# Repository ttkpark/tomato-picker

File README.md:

# tomato-picker

LG Physical AI 부스용 **토마토 따기 로봇** 데모 소프트웨어.
음성/텍스트 명령을 Claude가 받아 → 로봇이 색검출로 익은 토마토를 찾고 →
직접 따서 바구니에 담는다. (개념: *"언어 → 인식 → 행동"*)

> 설계 원칙: AI는 **두 층**(① 색 기반 열매 인식 ② Claude 함수콜 계획)에만.
> 이동·집기 등 저수준 동작은 **결정적 스킬 함수**로 처리한다.
> 자세한 배경은 [스마트로봇_명세서.md](스마트로봇_명세서.md), [PROJECT_토마토로봇.md](PROJECT_토마토로봇.md) 참고.

## 구조

```
main.py                         진입점 (demo / run)
src/tomato_picker/
├── config.py                   나무 위치·색 임계값·모델 ID
├── skills.py                   스킬 함수 5종 (핵심 API)
├── orchestrator.py             Claude tool-use 루프 (온라인)
├── demo_mode.py                오프라인 자동 시퀀스 (폴백, 필수)
├── hardware/                   하드웨어 추상화
│   ├── base.py                 인터페이스 (Base/Arm/Camera)
│   ├── mock.py                 PC용 Mock 구현
│   └── jetson.py               젯슨(실장비) 구현
└── vision/
    ├── color_detect.py         HSV 색검출 (빨강=익음/초록=미익음)
    └── claude_vision.py        Claude 비전 보조

firmware/mecanum_stable/        ✅ 현재 주행 펌웨어 (젯슨 시리얼 V/S 프로토콜, 데드맨+워치독) → firmware/README.md
tools/mirror_toggle.py          젯슨: SO-101 미러링 + 모션 프리셋 (PS2/키보드 연동, 리더 필요)
```

핵심: 스킬 함수 5종(`drive_to_tree` · `scan_tree` · `pick_fruit` ·
`place_in_basket` · `home`)을 온라인(Claude)과 오프라인(데모) 경로가
**공유**하므로 두 모드의 동작이 일관된다.

## 설치

```powershell
python -m venv .venv
.\.venv\Scripts\Activate.ps1
pip install -r requirements.txt
```

## 실행

```powershell
# 오프라인 데모 (망/API 키 불필요) — 지금 바로 실행 가능
python main.py demo

# Claude 오케스트레이션 (.env에 ANTHROPIC_API_KEY 필요)
copy .env.example .env   # 키 입력
python main.py run "익은 토마토 다 따줘"
```

현재는 **Mock 하드웨어**로 동작한다(합성 영상으로 색검출까지 전부 검증).
실제 장비가 오면 `main.py`의 `build_robot()`에서 하드웨어 구현만 교체한다.

## 하드웨어 제어 (실장비 — 메카넘 베이스 + SO-101 팔)

실장비는 **젯슨 Orin Nano**(JetPack)에서 구동한다. 두 갈래로 제어한다:

- **메카넘 베이스 + 팔 보조 입력** — Moebius Uno + PS2 패드. 펌웨어
  [firmware/PS2-MOTOR](firmware/PS2-MOTOR/) 가 PS2로 본체를 직접 굴리고, L1/R1 버튼은
  시리얼로 젯슨에 신호를 보낸다. 빌드·조작·핀맵은 [firmware/README.md](firmware/README.md).
- **SO-101 팔 (LeRobot)** — 리더→팔로워 텔레오프 미러링 + 모션 프리셋.
  젯슨에서 [tools/mirror_toggle.py](tools/mirror_toggle.py) 실행:

  | 조작 | 동작 |
  |---|---|
  | PS2 방향키 / □○ | 본체 주행 / 평행이동 |
  | **L1** | 팔 미러링 ON(리더 추종) ↔ OFF(limp) 토글 |
  | **R1 + △○✕□** | 미러링 ON: 현재 자세 **저장** / OFF: 저장 자세 **재생** (슬롯 1~4) |

  프리셋은 `~/arm_presets.json`에 영속. **토마토 따기 = 프리셋 1→2→3→4 순차 재생.**

> 셋업 메모(LeRobot 설치, 모터 ID·캘리브레이션, wrist_roll 엔코더 보정, CH340 드라이버
> 빌드 등)는 개발자 노트 참조. 실장비 구현은 `hardware/jetson.py`.

## 다음 단계

- [x] SO-101 팔 셋업(모터 ID·캘리브레이션) + 텔레오프 미러링 + 모션 프리셋
- [x] 메카넘 베이스 PS2 주행 펌웨어
- [ ] 모션 프리셋 시퀀스 **원버튼 자동 재생**(1→2→3→4) — 반복 수확
- [ ] 비전(토마토 검출) → 팔 동작 좌표 연동 / 시퀀스 자동 트리거
- [ ] `hardware/jetson.py`를 스킬 함수(`pick_fruit` 등)에 완전 연결
- [ ] 색 임계값을 실제 조명/열매로 튜닝 (`config.py`)
- [ ] (선택) 음성 입력(STT) → `run` 명령 연결

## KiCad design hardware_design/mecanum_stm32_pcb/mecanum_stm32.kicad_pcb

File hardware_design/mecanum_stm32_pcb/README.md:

# 메카넘 STM32 주행보드 (Uno + Moebius 쉴드 대체)

[docs/stm32-자세보드-목표.md](../../docs/stm32-자세보드-목표.md) 2단계(G2 엔코더 4채널 + G4 전원 도메인 분리)를 하는 보드.
펌웨어 = [firmware/mecanum_stm32/](../../firmware/mecanum_stm32/) (mecanum_stable v2.1 프로토콜 그대로 → 젯슨 코드 수정 없음).
요구사항 = [명세서 v0.2](../../docs/STM32_메카넘_베이스컨트롤러_명세서.md) (v0.1 항목별 반영 결과는 거기 §6).

- `gen_pcb.py` = **회로도 겸 배치**. 부품·넷·자리를 여기서 정하고 돌리면 `mecanum_stm32.kicad_pcb`가 다시 나온다.
  `"C:/Program Files/KiCad/9.0/bin/python.exe" gen_pcb.py` (겹침 0이어야 끝). `.kicad_sch`는 없다.
- 지금 상태(2026-11-09 **검토 반영 개정**): 148부품(고정구멍 포함), 선분 1,970 · 비아 160 — **kicad-cli DRC 오류 0 · 미연결 0**(`--severity-error`),
  `route.py check` 통과: 선 ≥0.127mm(최소 0.127) · 드릴 ≥0.3mm(최소 0.30) · USB 넷↔나머지 동박 ≥1.50mm · 디커플링 최악 2.85mm(≤3).
  전원 면 최소 폭(F.Cu, 1oz 기준 판단): VBAT_IN 2.6 · VBAT_R 2.4 · VBAT_P 2.4(K1 COM까지 3.2) · VM 릴레이→각 드라이버 탭 2.4 ·
  탭→핀 11 0.97(핀 끝에서 ≈1.65mm는 0.45mm 넥 — 핀 12·10 사이로 들어가는 입구) · 모터 출력 1.0mm(패드에서 0.76mm만 0.4mm 넥).
  거버 = [`gerber/`](gerber/)(2026-11-09 재생성, 같은 층·드릴 옵션). `placement.png` = 윗면 3D 렌더. 케이스 v2의 100×70 칸·Uno 구멍 그대로.
  **11/09에 바뀐 것과 이유**(검토 보고 → 결정):
  · 배치를 절대 mm로 다시 — 예전엔 Uno 비율로 늘린 좌표 + 30mm 나선 정착이라 U12 차지펌프 캡이 34mm, VCAP1 17mm, 크리스털 13mm 떨어져 있었다.
    IC마다 디커플링·타이밍 부품을 핀 기준 상대 좌표로 묶어 고정하고, 정착은 3mm 이내·고정 부품 불가, **배치 뒤 거리 검사(3mm)가 실패하면 종료코드 1**.
    예외: 드라이버 VM 벌크 C43/C47/C51/C55(10µF)는 핀 11에서 ≈4.1mm — 100nF(C42 등)가 1.9mm에 있고 차지펌프 캡 셋과 출력선이 3mm 안을 다 쓴다.
  · 전원: 예전 VM 0.19mm·VBAT_P 0.3mm 병목(정지 시 9.2A) → **F.Cu 동박 면**(VBAT_IN/VBAT_R/VBAT_P/VM: 위·아래 가장자리 띠 + 오른쪽 기둥 + 드라이버마다 탭).
    전원 넷은 Freerouting이 배선하지 않는다 — 그 넷 패드를 전부 면 안에 두었다(R9·R11·R66·D3·C15·D1·R1 자리 이동). 모터 출력은 gen_pcb가 1.0mm로 미리 깐다.
  · B.Cu는 GND 동박이지만 신호 2층 배선이라 **통짜는 아니다**(B.Cu 신호선 ≈1.9m, GND 채움 ≈3,950mm² ≈ GND 칸의 60%, 7조각 — 모두 비아로 이어짐).
  · DFM: DRV8874 방열 비아 0.2mm×48 → **0.3/0.6mm×12**(비아 없는 풋프린트 + 스크립트가 넣음). 설계규칙(.kicad_pro): 선 0.127·드릴 0.3·비아 0.6·간격 0.13.
  · 절연: U5를 회전 0으로(1~4번=USB 칸) — 예전엔 90°라 GNDU·GND 동박이 0.2mm까지 붙어 있었다. Freerouting에 1.5mm 해자(양면 금지)를 주고, `check`가 USB 넷↔나머지 동박 거리를 잰다.
  · 회로: 소프트 스타트·R1 22k·AMS1117 탄탈·E-stop PTC·코일 제너·ADC 100nF·VDDA 2.2µF·15pF·15µH·출력 22µF×3·Cin 100nF·USBLC6(부품 표는 아래).
- 다시 만들기 (순서 중요 — `gen_pcb.py`가 저장하며 `.kicad_pro` 넷클래스를 덮어쓰고, `route.py`가 다시 넣는다):
  ```
  K="C:/Program Files/KiCad/9.0/bin/python.exe"
  "$K" gen_pcb.py                 # 배치(빈 판)
  FR="java -jar freerouting-2.5.0.jar --router.autorouter.max_passes=60 --router.optimizer.enabled=false --gui.enabled=false"
  "$K" route.py prep              # 넷클래스·설계규칙 + mecanum_stm32.dsn (1단계: 전원 면 = 무른 plane)
  $FR -de mecanum_stm32.dsn -do stage1.ses
  "$K" route.py prep2 stage1.ses  # 2단계: 전원 면 = F.Cu 금지 구역, 면을 침범한 1단계 배선만 빼고 씨앗으로
  $FR -de mecanum_stm32.dsn -do mecanum_stm32.ses
  #   ⚠ optimizer를 켜 두면 최적화 단계에서 멈춰 .ses가 안 써진다(2026-11-02, 3회)
  #   ⚠ 1단계만 쓰면 Freerouting이 plane을 '나중에 다시 채울 동박'으로 보고 다른 넷을 그 위로 지나가게 해 전원 면이 끊긴다.
  #     처음부터 금지 구역으로 주면 배선이 발산한다(미배선 30~170을 오감) → 두 단계(11/09)
  "$K" route.py finish            # .ses 가져오기 → 가는 조각·곁가지 굵히기 → 전원 면(F.Cu) + GND 동박(양면) → 저장
  "$K" route.py check             # 선 ≥0.127 · 드릴 ≥0.3 · 절연 1.5mm · 디커플링 3mm · 전원 면 최소 폭
  kicad-cli pcb drc --severity-error --exit-code-violations mecanum_stm32.kicad_pcb
  ```
  `gen_pcb.py`는 겹침·절연 칸·**디커플링 거리(IC 핀 패드 ↔ 부품 패드 가장자리 ≤3mm)** 중 하나라도 어기면 종료코드 1로 멈춘다.
  배치를 안 바꿨으면 Freerouting 없이 저장소의 `mecanum_stm32.ses`(2단계 결과)로 `gen_pcb.py` → `route.py finish`만 하면 같은 판이 나온다.
  ⚠ KiCad 9.0.4의 `pcbnew.ExportSpecctraDSN`은 헤드리스에서 멈춰서 DSN/SES 변환을 `route.py`에 직접 짰다.

## 무엇을 왜 골랐나

| 자리 | 부품 | 왜 |
|---|---|---|
| MCU | **STM32F405RGT6** (LQFP64 0.5mm) | 엔코더 모드 타이머 4개(TIM2·3·4·5)를 다 쓰고도 PWM용 TIM8(4ch)·TIM9·TIM12가 남는다. F103은 TIM1~4뿐이라 엔코더 4개를 쓰면 PWM이 없고, F411은 TIM8이 없어 PWM이 TIM1(=USART1 PA9/PA10)과 겹친다. 엔코더 핀은 전부 5V 톨러런트(FT) |
| 모터 드라이버 ×4 | **DRV8874PWPR** (HTSSOP-16) | VM 37V(레일 12.6V의 ×2.9 — 목표 G4 "≥1.5배"), 6A 피크, **IPROPI 전류 감지 → ADC**, **nFAULT**, 내부 전류 제한(VREF). 지금 HR8833은 10.8V 정격에 12V를 물려 7/29에 탔다 |
| 젯슨 링크 | **CH340C + ADuM1201** | CH340C는 USB 전원(VBUS)으로, ADuM1201이 UART 두 가닥만 건넌다 → **젯슨 GND와 모터 GND가 끊긴다**(USB 끊김 `-71`의 원인 = 접지 루프). 칩이 CH340이라 젯슨에선 똑같이 `/dev/ttyUSB0`(1a86:7523). DTR을 안 물려서 **포트를 열어도 리셋되지 않는다**(Uno는 리셋됐다) |
| 전원 스위치 | **Q1·Q4 AO4407A 소스 맞댄 쌍** + **J8** 2핀 헤더(잠금형 스위치) + **소프트 스타트**(C15 1µF·D9·R71) | 스위치는 게이트만 GND로 당긴다(R1 22k/R68 10k → Vgs −0.69·Vbat: 7.4V→−5.1V, 12.6V→−8.7V, 24V는 D1 12V 클램프). C15가 **켤 때만**(D9) Q4 게이트-드레인 밀러 용량으로 걸려 VBAT_P를 ≈0.8V/ms로 올린다 → 2.5mF 돌입 ≈2A·≈15ms(예전엔 하드 스위칭 수십~100A대). 끌 때는 D9가 막아 밀러가 R71 100k로만 걸리므로 부하 중에 꺼도 FET가 선형 구간에 오래 머물지 않는다 → 배터리 전류가 스위치를 안 지나 작은 패널 스위치로 되고, 꺼지면 대기전류 0. FET 하나로는 몸체다이오드로 새서 못 끈다. 선이 빠지면 꺼진다. ⚠ 이 보드만 끈다 — 젯슨이 따로 배터리에서 받으면 같이 안 꺼진다 |
| 전압 감시 | 배터리 PC4 · 모터 VM PC5(100k/10k) · **5V PB0**(10k/10k) · **3V3 = VREFINT**(핀 없음), 분압점마다 100nF(C35~C37) | 100k/10k(9.1kΩ)는 ADC 샘플링 15사이클(21MHz)에서 겨우 들어간다 → 100nF가 전하를 대 준다.  하트비트 `vin= vm= v5= v33=`(mV) → 대시보드 비상정지 카드에 계통별 V. 상태 LED는 PB0→PB11로 옮겼다 |
| 전원 | AO4407A 역접속 보호(+스위치) → **VBAT_P**(1000µF 35V ×2, 배터리 감지 100k/10k) → **릴레이 K1** → VM(+SMBJ15A TVS) / VBAT_P → **SS34 + 470µF 홀드업** → **TPS542025**(5V 고정 벅, 4.5~30V) → AMS1117-3.3(출력 22µF 탄탈 C34 — AMS1117 안정 조건 ESR) | TPS542025: L1 **15µH**(TI 5V 표값) · 출력 22µF×3 · 입력 10µF+100nF를 VIN 핀 3mm 안에. 모터 기동으로 VM이 처져도 로직은 다이오드 뒤 홀드업으로 버틴다(지금 쉴드는 XL1509가 같이 무너져 BOD 리셋). 로직은 **릴레이 앞**에서 따서 비상정지 중에도 MCU·링크가 산다. 5V는 엔코더 전원(VCC50)도 겸한다 |
| 비상정지 | **K1 SRD-05VDC-SL-C**(10A/28VDC) + **F1 PTC 0.2A**(5V → E-stop 선, 선이 눌려 GND에 닿아도 5V 레일이 안 무너진다) + J6 단자(외부 NC 버튼, 없으면 단락) + 코일 역기전력 **D7 1N4148W + D8 12V 제너**(음극끼리 직렬 → 코일이 −12.5V까지 내려가 접점이 빨리 떨어진다. PB13엔 R60 10k 너머 ≈1.2mA 음주입 — F4 FT 핀 한계 5mA 안) + 코일 감지 → PB13 + **릴레이 뒤 VM 감지 → PC5**(100k/10k, 접점 용착 검출) + **VM 방전 2kΩ**(R66+R67 1k×2, E-stop 때 VM을 ≈80 ms에 비워 용착 오판 방지) | 명세서: 버튼이 릴레이 코일(5V)을 끊으면 접점이 **VM을 물리적으로 끊는다**(MCU 무관). 벌크는 릴레이 **앞**(뒤에 두면 접점이 닫힐 때 돌입 전류로 붙을 수 있다) |
| 엔코더 | 1k 직렬 + 10k 풀업(3V3) → 타이머 엔코더 모드 | 인터럽트로 세지 않는다(펄스 손실 0, G2). 오픈컬렉터/푸시풀 둘 다 받는다. **실측(11/04)**: 모터 엔코더 C1·C2 = 0↔5V, GND 단락 전류 ≈500µA(±5%) → **모터 안에 10k 풀업(5V)이 있는 오픈컬렉터**, C1−C2 = +5/0/−5V(0V 구간 있음) → **2상(90°) 확인**. 낮음일 때 VCC 단락 112·120mA = 출력 트랜지스터가 제한 없이 끌어내린다 → 보드 쪽 **1k 직렬이 핀 오설정(출력 HIGH) 때 3.3mA로 막아 준다 — 빼지 말 것**. 커넥터 1~6번 핀 중심 10mm = **2.0mm 피치 → PH 2.0 6핀 확인**(J10~J13 그대로). 보드의 3V3 10k 풀업과 겹쳐도 핀은 높음 ≈4.1V(FT 핀이라 됨)·낮음 ≈0.5V(VIL ≈1V 아래), 3V3로 역류는 채널당 ≈80µA |
| 커넥터 | JST PH 6핀 ×4, 쉴드와 같은 순서 `M− · GND · ENC_B · ENC_A · 5V · M+` | 모터 선을 그대로 옮겨 꽂게. **11/04 대조 완료**: 쉴드 회로도 [ARDUINO_HR8833.pdf](../../firmware/MecanumRobot-Arduino-Uno-master/ARDUINO_HR8833.pdf) JP1 `1 M1− · 2 GND · 3 ENCODER1_B · 4 ENCODER1_A · 5 VCC50 · 6 M1+` = J10~J13 1~6번과 같다, 실물 플러그 핀 중심 10mm·하우징 폭 13.5mm = PHR-6(PH 2.0), 장바구니 16721463 = JST 정품 B6B-PH-K-S. 쉴드는 JP3·JP4 엔코더가 NC였지만 이 보드는 4개 다 받는다 |
| USB | **Mini-B**(Würth 65100516121, 0.8mm 피치 5핀 + 큰 고정탭) + **USBLC6-2SC6**(D+/D−/VBUS ESD, GNDU 쪽) | USB-C는 0.5mm 피치라 손땜이 어려워 바꿨다(CC 저항도 필요 없다). 완전 스루홀이 필요하면 Tensility 54-00023(세로형) |
| 젯슨 UART 직결(대안) | **J7** 1×4 헤더(GNDU · TX→ · ←RX · 3.3V) + R62~R64 0Ω | 명세서의 "젯슨 3.3V UART 직결"을 **절연기 앞**에 붙였다(젯슨 GND는 GNDU 칸에만 닿는다). 기본은 USB(R62~R64 실장). J7로 쓸 땐 R62~R64를 빼고 젯슨 포트를 `/dev/ttyTHS*`로 |
| 기타 | SWD 헤더, RESET/BOOT0 버튼, I²C 헤더(MPU6050 이전용), SPI IMU 헤더(오른쪽 헤더 줄), LED 3개 | 첫 굽기는 SWD 또는 BOOT0. 이후엔 젯슨에서 `U` 명령 → `stm32flash` |

판 = **100×70mm, 2층**. 고정구멍 4개는 **Uno와 같은 자리**(왼쪽 아래 기준)라 지금 스탠드오프에 앉는다.
Uno 크기(68.6×53.3)로는 2층 배선이 안 나와 키웠고(부품면적 67%), 명세서 반영(릴레이·벌크)으로 90×64에서 한 번 더 키웠다(지금 46%).

## 부품 주문 — 엘레파츠 장바구니 (2026-11-02, 34종 74,011원·무료배송, 발송 예정 11/13)

예비 포함 수량. 상품번호 = `https://www.eleparts.co.kr/goods/view?no=<번호>`.
디바이스마트는 조회 중 접속이 막혀(연속 요청 차단으로 보임) 이번엔 안 썼다.
⚠ **비회원 장바구니는 세션 쿠키라 브라우저를 닫으면 사라진다**(실제로 한 번 날아가 다시 담았다) — 로그인해서 담을 것.

| 품목 | 상품번호 | 수량 | 기판 |
|---|---|---|---|
| STM32F405RGT6 | 12074516 | 2 | U1 |
| DRV8874PWPR | 12217360 | 5 | U10~U13 |
| TPS542025DDCR | 18672221 | 2 | U2 |
| AMS1117-3.3 (UMW) | 7595038 | 10 | U3 |
| CH340C | 6557221 | 2 | U4 |
| ADUM1201ARZ (ADI) | 18290182 | 1 | U5 |
| AO4407A | 12744910 | 5 | Q1·Q4 |
| SMBJ15A (Littelfuse) | 6978442 | 5 | D2 |
| SS34 | 17819449 | 20 | D3, D7 |
| BZT52C12 | 16812906 | 5 | D1 |
| 8MHz 3225 12pF | 12209546 | 5 | Y1 |
| SRP7028A-100M 10µH | 2840708 | 2 | L1 |
| 470µF 25V 10×12.5 | 3369549 | 5 | C2 |
| 1000µF 35V 12.5×20 (삼영 KMG) | 9159533 | 5 | C1, C14 |
| 릴레이 SRD-05VDC-SL-C | 8570092 | 2 | K1 |
| USB Mini-B Würth 65100516121 | 69486 | 2 | J2 |
| JST B6B-PH-K-S | 16721463 | 5 | J10~J13 |
| KF301-5.0-2P | 10367448 | 5 | J1, J6 |
| B3F-1000 | 18219995 | 2 | SW1, SW2 |
| 핀헤더 1×40 | 16069834 | 1 | J3·J4·J5·J7·J8 (잘라 씀) |
| 0603 저항 10k / 1k / 47k / 100k / 0Ω | 9845055 / 9471061 / 16762241 / 16790845 / 14720542 | 각 100 | |
| 0603 100nF 50V / 22nF 50V / 2.2µF / 4.7µF / 20pF | 8010073 / 8010651 / 8011085 / 8010241 / 8010017 | 100/50/50/10/100 | |
| 1206 10µF 25V / 22µF 10V | 8010168 / 8010994 | 10 / 5 | |
| 0603 LED 초록 / 빨강 | 4996 / 4997 | 각 5 | D4·D5 / D6 |

### 2026-11-09 검토 반영으로 늘거나 바뀐 부품 — 11/09 비서가 로그인 계정 장바구니에 담음(9종 ≈12,612원, VAT 별도)

상품번호: SRP7028A-150M 12432675 · USBLC6-2SC6 18086957 · 탄탈 22µF 3528 6533815 · PTC 0.2A 0ZCJ0020FF2E 18218454 · 0603 15pF 2638972 · 0603 22k 18136622 · 0805 1µF 50V 18068538 · 1N4148W 16865523 · BZT52C12 17312667(3개).
⚠ 비서는 담을 때 **장바구니에 SRP7028A-100M·BZT52C12가 없었다**고 했다 — 11/02의 34종이 비회원 세션째 날아갔을 수 있다. 결제 전에 위 표와 대조할 것.

| 품목 | 수량(예비 포함) | 기판 | 비고 |
|---|---|---|---|
| SRP7028A-**150M** 15µH | 2 | L1 | 100M(10µH) 대신, 같은 풋프린트. 장바구니의 100M은 빼도 된다 |
| USBLC6-2SC6 | 3 | U6 | USB ESD |
| 22µF 10V 탄탈 EIA-3528(B) | 3 | C34 | AMS1117 출력 ESR |
| PTC 0.2A hold 1206 (예: Bel 0ZCJ0020FF2E) | 3 | F1 | 5V → E-stop 선. 코일 71mA에 R≤4Ω → 코일 4.7V 이상 |
| 0603 15pF | 10 | C28, C29 | 20pF 대신(CL 12pF 수정) |
| 0603 22k | 10 | R1 | 100k 대신 |
| **0805 1µF 50V X7R** | 5 | C15 | 소프트 스타트(지시의 47nF 대신 — 아래 이유) |
| 1N4148W (SOD-123) | 10 | D7, D9 | D7은 SS34(SMA) 대신 — 코일 71mA |
| BZT52C12 | +3 (총 8) | D8 | 장바구니 5개 → D1·D8 |
| 0603 100nF / 2.2µF / 22µF 1206 | 기존 수량 안 | C32·C35~C37 / C31 / C33 | 장바구니 수량으로 충분 |
| 0603 0Ω / 100k / 47k | 기존 수량 안 | R72~R74(칩마다 PMODE) / R75 / R76(아래 줄 VREF) | 장바구니 수량으로 충분 |

47nF가 아니라 1µF+다이오드인 이유: 게이트-드레인 47nF(R68 10k)면 VBAT_P가 ≈18V/ms로 올라 2.5mF 돌입이 ≈45A·0.7ms가 되고,
그동안 콘덴서 충전 에너지(½CV² ≈0.2J)를 **FET가 1ms 안에 다 먹는다**(SOIC-8 1ms SOA 밖일 공산이 크다, AO4407A SOA 그래프로 확인 요) —
하드 스위칭보다 나쁘다. 또 밀러 C가 끌 때도 걸려 22k로 끄면 부하 중 ≈4ms 선형 구간. 그래서 C15 1µF(≈15ms 램프, 돌입 ≈2A, FET 평균 ≈13W)를
D9로 **켤 때만** 걸고 R71 100k가 꺼진 뒤 원위치시킨다.

VREF·PMODE: 한 넷을 판 네 귀퉁이 드라이버로 끌면 MCU 둘레가 막혀 자동배선이 끝나지 않아(11/09) **VREF 분압을 위(A·B: R13/R14)·아래(C·D: R75/R76) 줄에 하나씩**, PMODE 0Ω을 칩마다(R16·R72~R74) 두었다(값·동작은 같다).
재고가 없어 바꾼 값: 20k→**100k/47k**(VREF 1.06V, 전류제한 ≈2.3A), 4.7k→**10k**(I²C 풀업 — MPU6050 모듈에도 있다),
배터리 분압은 명세서대로 **100k/10k**(÷11, 36V까지 — 펌웨어 `B`의 기본 비 11000).

## ⚠ 만들기 전에 확인할 것

1. **모터에 엔코더가 정말 있나, 커넥터가 PH 2.0mm인가** — 쉴드 회로도상 6핀이지만 실물 확인 전([목표 문서 §0.1](../../docs/stm32-자세보드-목표.md)).
   2.54mm(XH)면 J10~J13 풋프린트만 바꾸면 된다.
2. ~~DRV8874 PMODE·IMODE~~ → **데이터시트(SLVSF66A, 42쪽)로 확인함**: PMODE=High → PWM 모드(표 2, nSLEEP가 올라갈 때 래치 —
   nSLEEP 풀다운이라 순서 OK), IN1=PWM·IN2=0 → 정방향/코스트(표 4, Uno와 같은 동작), IMODE=GND → 고정 오프타임 초핑 +
   과전류 **자동 재시도**(표 6), A_IPROPI 450µA/A.
3. **케이스** — 옛 트레이에선 100×70이 배터리 턱을 15.6mm 넘었다(11/05 계산). [케이스 v2](../case/README.md)는 앞 가운데에 이 판 자리를 뒀다(같은 구멍, 간섭 검사 통과) → 판을 다시 배치하지 않는다.
   제조 한계(11/09 개정): 선 ≥0.127mm, 드릴 ≥0.3mm(DRV8874 방열 비아 0.3/0.6mm × 12개/칩) — 설계규칙(.kicad_pro)이 DRC로 강제한다.
   **주문 메모: 동박 2oz 권장**(전원 면·모터선 저항·온도 절반).
6. **배터리가 24V면**(6S 만충 25.2V) — 바꿀 것: TVS SMBJ15A→SMBJ24A, 470µF 25V→35V, 1206 10µF 25V→50V(C3·C43 등),
   **블리더 R66/R67 0603(100mW)→1206** 또는 2.2k×2(25.2V에서 0603 각 159mW로 정격 초과), **Q1/Q4 → −40V P-FET**(AO4407A −30V는 84% 사용),
   소프트 스타트 C15 1µF→2.2µF(돌입 에너지 0.72J — 램프를 늘려 FET 평균 전력을 맞춘다), R1 22k는 그대로(D1이 Vgs −12V로 묶음).
   ⚠ SMBJ24A는 정격 펄스에서 Vc 38.9V로 DRV8874 권장 37V(절대 40V)를 넘는다 — 6S면 SMBJ 계열로는 맞는 게 없으니 클램프를 다시 고를 것.
   TPS542025(30V)·벌크(35V)·릴레이(28VDC)·분압(36V까지)은 그대로.
7. **선택 사항(이번엔 안 넣음)**: IPROPI에 10nF(데이터시트 허용, 코스트 감쇠라 IPROPI가 PWM으로 끊긴다 — 펌웨어 슬로 감쇠나 동기 샘플링이 우선),
   엔코더 커넥터 5V(5번 핀, M+ 바로 옆)에 퓨즈/PTC.
4. **HTSSOP 방열 패드** — 인두로는 안 붙는다. 열풍기/리플로우, 또는 방열 비아로 뒤에서 땜.
5. **자동배선 결과를 사람 눈으로 한 번** — 크리스털 주변, 절연 경계(GNDU 동박은 USB 칸에만, GND와 1.5mm), 게이트·소프트 스타트 망(손으로 깐 선).
   고정구멍 둘레 Ø6.5mm는 동박 금지(나사머리·스탠드오프가 GNDU를 로봇 GND에 잇지 않게).
   신호 0.15mm(Freerouting 넥다운 조각은 finish가 0.127 이상으로 되돌림), 5V·3V3·GND 곁가지는 간격이 되는 곳만 0.5mm.

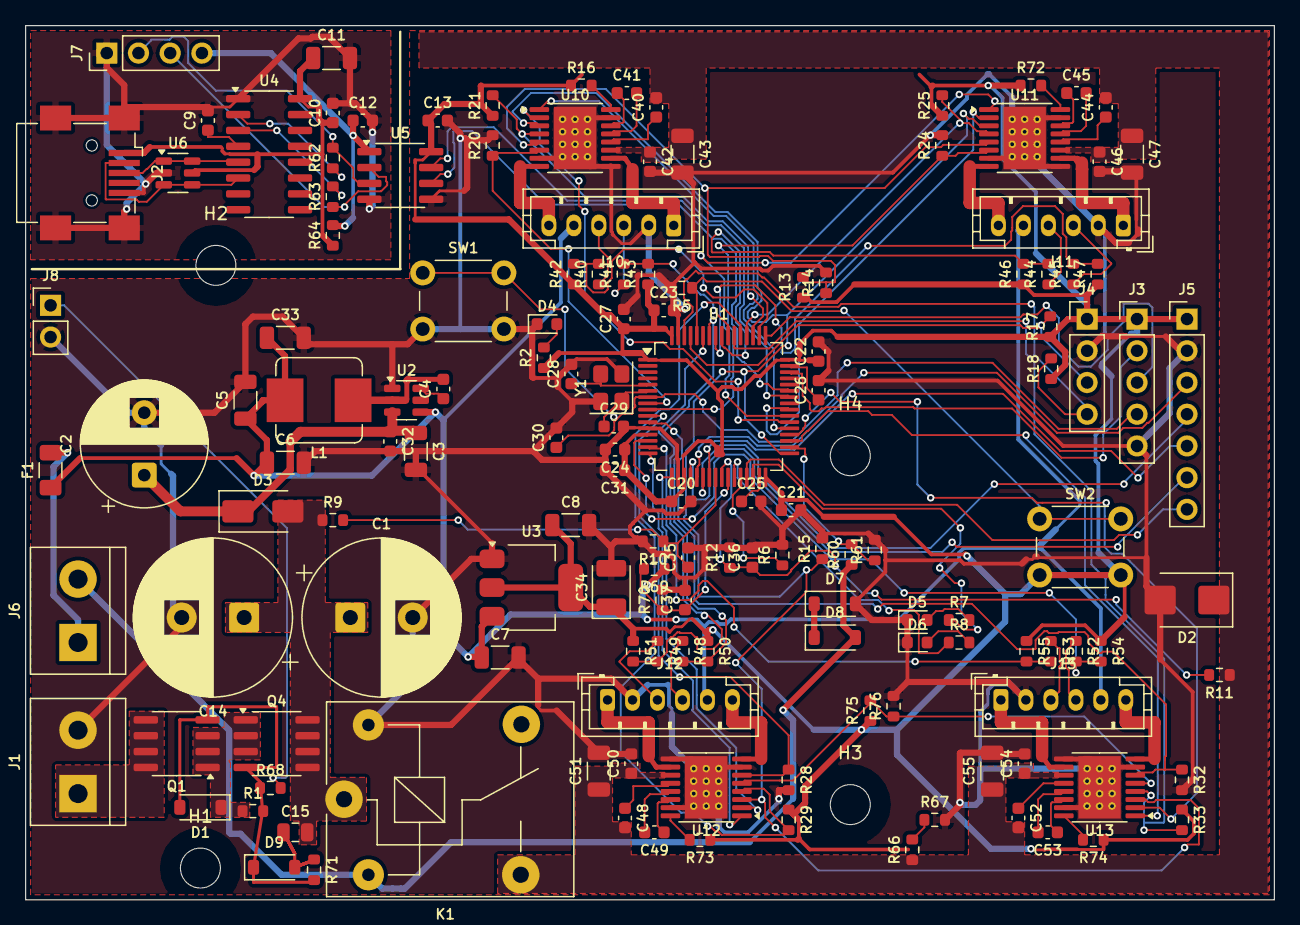
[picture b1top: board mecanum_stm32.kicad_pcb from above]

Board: 2 copper layers, 100.0 x 70.0 mm, 148 parts (0 on the bottom side), 113 nets.

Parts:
C1, C14: 1000u 35V; CP_Radial_D12.5mm_P5.00mm
C2: 470u 25V; CP_Radial_D10.0mm_P5.00mm
C3, C7, C8, C11, C43, C47, C51, C55: 10u 25V; C_1206_3216Metric
C4, C9, C10, C12, C13, C20, C21, C22, C23, C24, C30, C35, C36, C37: 100n; C_0603_1608Metric
C5, C6, C33: 22u 10V; C_1206_3216Metric
C15: 1u 50V X7R; C_0805_2012Metric
C25, C26, C31: 2.2u; C_0603_1608Metric
C27: 4.7u; C_0603_1608Metric
C28, C29: 15p; C_0603_1608Metric
C32, C40, C42, C44, C46, C48, C50, C52, C54: 100n 50V; C_0603_1608Metric
C34: 22u 10V tant; CP_EIA-3528-21_Kemet-B
C41, C45, C49, C53: 22n 50V; C_0603_1608Metric
D1, D8: BZT52C12; D_SOD-123
D2: SMBJ15A; D_SMB
D3: SS34; D_SMA
D4: PWR 초록; LED_0603_1608Metric
D5: 상태 초록; LED_0603_1608Metric
D6: 고장 빨강; LED_0603_1608Metric
D7, D9: 1N4148W; D_SOD-123
F1: PTC 0.2A hold; Fuse_1206_3216Metric
H1, H2, H3, H4: MountingHole_3.2mm_M3
J1: BAT 7.4~12.6V; TerminalBlock_bornier-2_P5.08mm
J2: USB Mini-B; USB_Mini-B_Wuerth_65100516121_Horizontal
J3: SWD; PinHeader_1x05_P2.54mm_Vertical
J4: I2C (MPU6050); PinHeader_1x04_P2.54mm_Vertical
J5: SPI IMU; PinHeader_1x07_P2.54mm_Vertical
J6: E-STOP (NC); TerminalBlock_bornier-2_P5.08mm
J7: JETSON UART; PinHeader_1x04_P2.54mm_Vertical
J8: POWER SW; PinHeader_1x02_P2.54mm_Vertical
J10: MOTOR A; JST_PH_B6B-PH-K_1x06_P2.00mm_Vertical
J11: MOTOR B; JST_PH_B6B-PH-K_1x06_P2.00mm_Vertical
J12: MOTOR C; JST_PH_B6B-PH-K_1x06_P2.00mm_Vertical
J13: MOTOR D; JST_PH_B6B-PH-K_1x06_P2.00mm_Vertical
K1: SRD-05VDC-SL-C; Relay_SPDT_SANYOU_SRD_Series_Form_C
L1: 15uH SRP7028A-150M; L_Bourns_SRP7028A_7.3x6.6mm
Q1, Q4: AO4407A; SOIC-8_3.9x4.9mm_P1.27mm
R1: 22k; R_0603_1608Metric
R2, R7, R8, R20, R24, R28, R32, R40, R41, R44, R45, R48, R49, R52, R53, R66, R67: 1k; R_0603_1608Metric
R5, R6, R10, R12, R17, R18, R21, R25, R29, R33, R42, R43, R46, R47, R50, R51, R54, R55, R60, R68, R69, R70: 10k; R_0603_1608Metric
R9, R11, R13, R15, R61, R71, R75: 100k; R_0603_1608Metric
R14, R76: 47k; R_0603_1608Metric
R16, R62, R63, R64, R72, R73, R74: 0; R_0603_1608Metric
SW1: RESET; SW_PUSH_6mm
SW2: BOOT0; SW_PUSH_6mm
U1: STM32F405RGT6; LQFP-64_10x10mm_P0.5mm
U2: TPS542025 (5V); SOT-23-6
U3: AMS1117-3.3; SOT-223-3_TabPin2
U4: CH340C; SOIC-16_3.9x9.9mm_P1.27mm
U5: ADuM1201ARZ; SOIC-8_3.9x4.9mm_P1.27mm
U6: USBLC6-2SC6; SOT-23-6
U10, U11, U12, U13: DRV8874PWPR; HTSSOP-16-1EP_4.4x5mm_P0.65mm_EP3.4x5mm_Mask2.46x2.31mm
Y1: 8MHz 3225 12pF; Crystal_SMD_3225-4Pin_3.2x2.5mm

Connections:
3V3: C8.1, C13.1, C20.1, C21.1, C22.1, C23.1, C24.1, C27.1, C31.1, C34.1, J3.1, J4.1, J5.1, R2.1, R13.1, R16.1, R17.1, R18.1, R21.1, R25.1, R29.1, R33.1, R42.1, R43.1, R46.1, R47.1, R50.1, R51.1, R54.1, R55.1, R72.1, R73.1, R74.1, R75.1, SW2.2, U1.1, U1.13, U1.19, U1.32, U1.48, U1.64, U3.2, U5.8
5V: C5.1, C6.1, C7.1, C33.1, F1.1, J10.5, J11.5, J12.5, J13.5, L1.2, R69.1, U2.4, U3.3
BLD: R66.2, R67.1
BOOT0: R5.1, SW2.1, U1.60
BOOT1: R6.1, U1.28
BST5: C4.1, U2.6
COIL: D8.2, J6.2, K1.2, R60.1
CPH_A: C41.2, U10.13
CPH_B: C45.2, U11.13
CPH_C: C49.2, U12.13
CPH_D: C53.2, U13.13
CPL_A: C41.1, U10.14
CPL_B: C45.1, U11.14
CPL_C: C49.1, U12.14
CPL_D: C53.1, U13.14
DM: J2.2, U4.6, U6.3, U6.4
DP: J2.3, U4.5, U6.1, U6.6
EAA: J10.4, R40.1
EAB: J10.3, R41.1
EBA: J11.4, R44.1
EBB: J11.3, R45.1
ECA: J12.4, R48.1
ECB: J12.3, R49.1
EDA: J13.4, R52.1
EDB: J13.3, R53.1
ENC_A_A: R40.2, R42.2, U1.50
ENC_A_B: R41.2, R43.2, U1.55
ENC_B_A: R44.2, R46.2, U1.56
ENC_B_B: R45.2, R47.2, U1.57
ENC_C_A: R48.2, R50.2, U1.58
ENC_C_B: R49.2, R51.2, U1.59
ENC_D_A: R52.2, R54.2, U1.14
ENC_D_B: R53.2, R55.2, U1.15
ESTOP: R60.2, R61.1, U1.34
ESTOP5: F1.2, J6.1
FLT_A: R21.2, U1.51, U10.4
FLT_B: R25.2, U1.52, U11.4
FLT_C: R29.2, U1.53, U12.4
FLT_D: R33.2, U1.54, U13.4
FLYK: D7.1, D8.1
GND: C1.2, C2.2, C3.2, C5.2, C6.2, C7.2, C8.2, C13.2, C14.2, C20.2, C21.2, C22.2, C23.2, C24.2, C25.2, C26.2, C27.2, C28.2, C29.2, C30.2, C31.2, C32.2, C33.2, C34.2, C35.2, C36.2, C37.2, C42.2, C43.2, C46.2, C47.2, C50.2, C51.2, C54.2, C55.2, D2.2, D4.1, D5.1, D6.1, D7.2, J1.2, J3.5, J4.2, J5.2, J8.2, J10.2, J11.2, J12.2, J13.2, K1.5, R5.2, R6.2, R10.2, R12.2, R14.2, R15.2, R20.2, R24.2, R28.2, R32.2, R61.2, R67.2, R70.2, R76.2, SW1.2, U1.12, U1.18, U1.63, U2.1, U3.1, U5.5, U10.7, U10.9, U10.15, U10.17, U11.7, U11.9, U11.15, U11.17, U12.7, U12.9, U12.15, U12.17, U13.7, U13.9, U13.15, U13.17, Y1.2, Y1.4
GNDU: C9.2, C10.2, C11.2, C12.2, J2.5, J2.6, J7.1, U4.1, U5.4, U6.2
I2C_SCL: J4.3, R17.2, U1.61
I2C_SDA: J4.4, R18.2, U1.62
IMU_INT: J5.7, U1.29
IPR_A: R20.1, U1.8, U10.6
IPR_B: R24.1, U1.9, U11.6
IPR_C: R28.1, U1.10, U12.6
IPR_D: R32.1, U1.11, U13.6
ISO_V1: C12.1, J7.4, R64.2, U5.1
LEDF: D6.2, R8.2
LEDP: D4.2, R2.2
LEDS: D5.2, R7.2
LED_FLT: R8.1, U1.27
LED_ST: R7.1, U1.30
MA+: J10.6, U10.8
MA-: J10.1, U10.10
MB+: J11.6, U11.8
MB-: J11.1, U11.10
MC+: J12.6, U12.8
MC-: J12.1, U12.10
MCU_RX: U1.43, U5.6
MCU_TX: U1.42, U5.7
MD+: J13.6, U13.8
MD-: J13.1, U13.10
NRST: C30.1, J3.4, SW1.1, U1.7
NSLEEP: R15.1, U1.33, U10.3, U11.3, U12.3, U13.3
OSC_IN: C28.1, U1.5, Y1.3
OSC_OUT: C29.1, U1.6, Y1.1
PMODE_A: R16.2, U10.16
PMODE_B: R72.2, U11.16
PMODE_C: R73.2, U12.16
PMODE_D: R74.2, U13.16
PWM_A1: U1.37, U10.1
PWM_A2: U1.38, U10.2
PWM_B1: U1.39, U11.1
PWM_B2: U1.40, U11.2
PWM_C1: U1.16, U12.1
PWM_C2: U1.17, U12.2
PWM_D1: U1.35, U13.1
PWM_D2: U1.36, U13.2
PWR_SW: J8.1, R68.2
Q_G: D1.2, D9.1, Q1.4, Q4.4, R1.2, R68.1, R71.2
SPI_CS: J5.6, U1.20
SPI_MISO: J5.4, U1.22
SPI_MOSI: J5.5, U1.23
SPI_SCK: J5.3, U1.21
SS: C15.1, D9.2, R71.1
SW5: C4.2, L1.1, U2.2
SWCLK: J3.3, U1.49
SWDIO: J3.2, U1.46
U_RX: J7.3, R63.1, U5.2
U_RXC: R63.2, U4.3
U_TX: J7.2, R62.2, U5.3
U_TXC: R62.1, U4.2
U_V3: C9.1, U4.4
V5_SNS: C37.1, R69.2, R70.1, U1.26
VBAT_IN: J1.1, Q1.5, Q1.6, Q1.7, Q1.8
VBAT_P: C1.1, C14.1, C15.2, D3.2, K1.1, Q4.5, Q4.6, Q4.7, Q4.8, R9.1
VBAT_R: D1.1, Q1.1, Q1.2, Q1.3, Q4.1, Q4.2, Q4.3, R1.1
VBUS: C10.1, C11.1, J2.1, R64.1, U4.16, U6.5
VB_SNS: C35.1, R9.2, R10.1, U1.24
VCAP1: C25.1, U1.31
VCAP2: C26.1, U1.47
VCP_A: C40.1, U10.12
VCP_B: C44.1, U11.12
VCP_C: C48.1, U12.12
VCP_D: C52.1, U13.12
VLOG: C2.1, C3.1, C32.1, D3.1, U2.3
VM: C40.2, C42.1, C43.1, C44.2, C46.1, C47.1, C48.2, C50.1, C51.1, C52.2, C54.1, C55.1, D2.1, K1.3, R11.1, R66.1, U10.11, U11.11, U12.11, U13.11
VM_SNS: C36.1, R11.2, R12.1, U1.25
VREF: R13.2, R14.1, U10.5, U11.5
VREF_CD: R75.2, R76.1, U12.5, U13.5

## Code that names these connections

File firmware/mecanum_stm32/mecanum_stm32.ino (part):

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const int8_t ENC_DIR[4] = {1, 1, 1, 1};   // ponytail: 상수 — 모터를 자주 바꾸게 되면 런타임 명령으로
const uint32_t PIN_NFAULT[4] = {PC10, PC11, PC12, PD2};
const uint32_t PIN_IPROPI[4] = {PC0, PC1, PC2, PC3};
#define PIN_NSLEEP PB12   // 4개 드라이버 공통. 기판 풀다운 → 펌웨어가 깨우기 전엔 출력 Hi-Z
#define PIN_VBAT   PC4    // 배터리(역접속 FET 뒤, E-stop 릴레이 앞) 100k/10k
#define PIN_ESTOP  PB13   // HIGH=릴레이 코일 붙음(모터 허용) / LOW=E-stop 눌림·버튼 회로 끊김 → VM 차단
#define PIN_VM     PC5    // 릴레이 **뒤** 모터 레일 VM, 100k/10k(배터리와 같은 비 — B의 ratio를 같이 쓴다)
#define PIN_V5     PB0    // 5V 레일 10k/10k. 3V3(VDDA)는 핀 없이 VREFINT로 잰다
#define PIN_LED    PB11   // 하트비트마다 깜빡
#define PIN_LEDF   PB1    // 드라이버 폴트
// 실측 보정 손잡이 — 저항 오차·IPROPI 편차는 여기서 맞춘다.
const uint32_t IPROPI_MA_PER_V = 2222; // 1kΩ × 450µA/A = 0.45V/A
const uint32_t V5_RATIO = 2000;        // ×1000 — 10k/10k
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  for(uint8_t i = 0; i < 4; i++) if(digitalRead(PIN_NFAULT[i]) == LOW) m |= 1u << i;
  for(uint8_t rise = m & ~fltMask; rise; rise >>= 1) fltCount += rise & 1;
  fltMask = m;
  digitalWrite(PIN_LEDF, m ? HIGH : LOW);
}

static uint32_t vdda(){
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//   (용착 방지). 디바운스는 여기선 안 한다: 잡음으로 한 번 서는 건 loop가 20ms 뒤 되살린다(estopPoll).
//   레지스터 직접 쓰기만 — HAL·Serial은 ISR에서 안 부른다.
void estopIsr(){
  GPIOB->BSRR = 1u << (12 + 16);                       // PB12 nSLEEP LOW → 출력 Hi-Z
  TIM8->CCR1 = 0; TIM8->CCR2 = 0; TIM8->CCR3 = 0; TIM8->CCR4 = 0;
  TIM9->CCR1 = 0; TIM9->CCR2 = 0;
  TIM12->CCR1 = 0; TIM12->CCR2 = 0;
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}

// 드라이버는 허용될 때만 깨어 있다 — nSLEEP는 이 한 곳에서만 쥔다.
static inline void updSleep(){ digitalWrite(PIN_NSLEEP, driversAllowed() ? HIGH : LOW); }

// E-stop: 20ms 디바운스로 이벤트. 눌림 → 래치. 풀림 → 보고만(래치 유지, S가 와야 깨운다).
void estopPoll(unsigned long now){
  bool raw = digitalRead(PIN_ESTOP) == LOW;
  if(raw != estopRaw){ estopRaw = raw; estopEdge = now; }
  bool stable = now - estopEdge >= ESTOP_DEBOUNCE;
  if(stable && raw != estop){
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  } else if(c == 'U'){
    // 바퀴부터 세운다. 드라이버도 재워 둔다 — 부트로더 동안 PWM 핀은 떠 있다.
    hardStop();
    digitalWrite(PIN_NSLEEP, LOW);
    Serial.println("ok U (시스템 부트로더 — stm32flash로 굽고 -g 0x08000000 으로 돌아옴)");
    Serial.flush();
    BT->enterBootloader = BOOTLDR_MAGIC;
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  latchBootInfo();          // RCC_CSR을 지우기 전에 확정 — 출력보다 먼저

  // 드라이버는 PWM이 0으로 자리 잡을 때까지 재워 둔다(기판 풀다운과 같은 쪽).
  pinMode(PIN_NSLEEP, OUTPUT); digitalWrite(PIN_NSLEEP, LOW);
  pinMode(PIN_LED, OUTPUT);    pinMode(PIN_LEDF, OUTPUT);
  for(uint8_t i = 0; i < 4; i++) pinMode(PIN_NFAULT[i], INPUT_PULLUP);
  pinMode(PIN_ESTOP, INPUT);    // 기판 100k 풀다운 — 선이 빠지면 LOW = E-stop 쪽으로 안전
  analogReadResolution(12);

  RCC->AHB1ENR |= RCC_AHB1ENR_GPIOAEN | RCC_AHB1ENR_GPIOBEN | RCC_AHB1ENR_GPIOCEN | RCC_AHB1ENR_GPIODEN;
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
  Serial.begin(115200);     // USART1 PA9/PA10 (build_opt.h — 기본 Serial은 UART4=PA0/PA1이라 엔코더 D와 겹친다)
  hardStop();
  estop = estopRaw = estopLatch = (digitalRead(PIN_ESTOP) == LOW);   // 켜질 때 이미 눌려 있으면 래치·재운 채로
  attachInterrupt(digitalPinToInterrupt(PIN_ESTOP), estopIsr, FALLING);
  updSleep();               // 허용이면 이제 깨운다 (tWAKE ~1ms, 그동안은 어차피 0)
  ensureBor();
  lastCmd = lastTick = lastLoop = millis();
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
